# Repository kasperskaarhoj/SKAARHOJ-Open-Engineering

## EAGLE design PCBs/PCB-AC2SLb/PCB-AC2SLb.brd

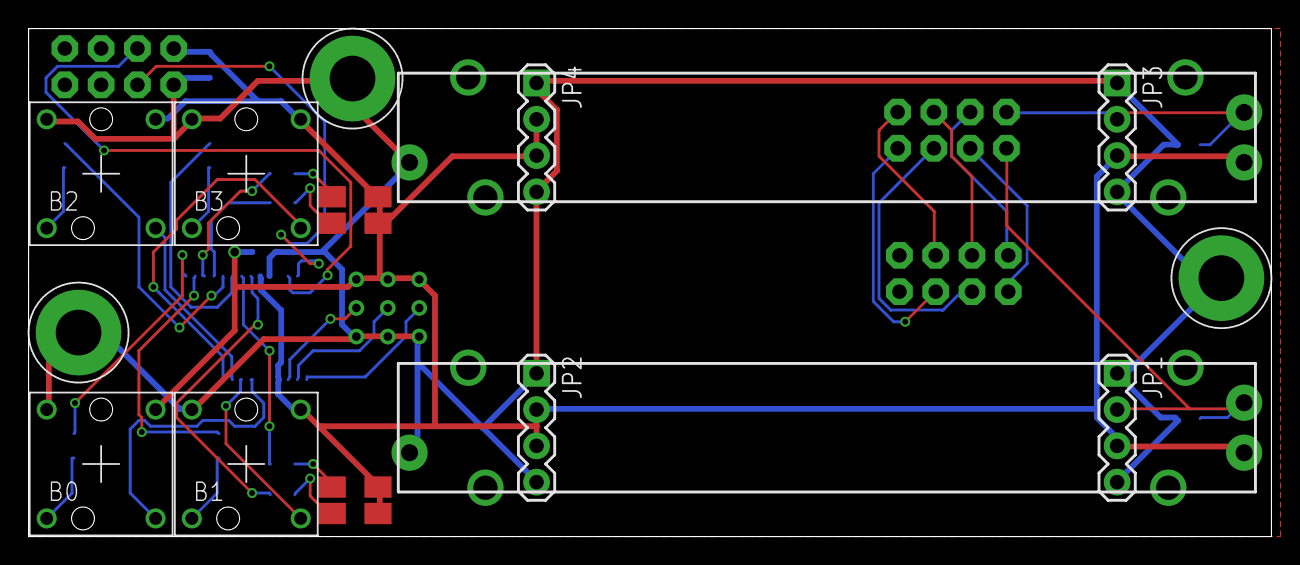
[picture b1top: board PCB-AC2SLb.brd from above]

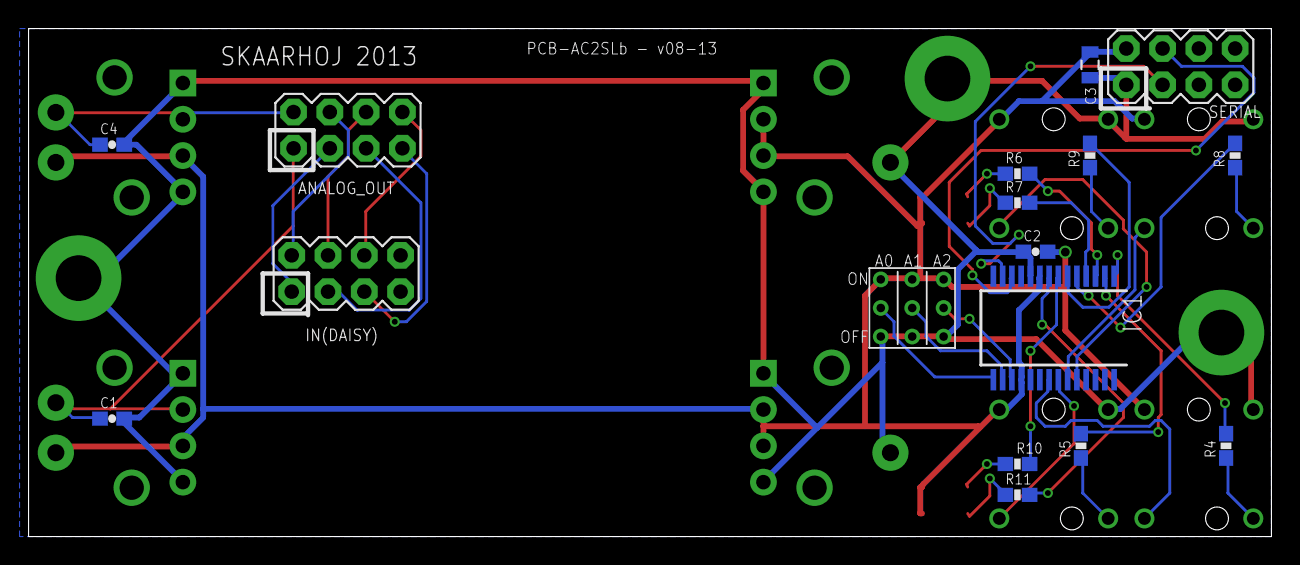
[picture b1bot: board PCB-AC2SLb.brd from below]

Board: 2 copper layers, 87.0 x 35.6 mm, 32 parts (17 on the bottom side), 35 nets.

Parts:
ANALOG_OUT: M04X2; 2X4
B0, B1, B2, B3: CFPB; CFPB-6/9MM
BILED1, BILED2: LEDBICOLOR-SMD
C1, C4: 10nF; 0603-CAP
C2: 100nF; 0603-CAP
C3: 10uF; 0805
IC1: MCP23017SS; SSOP28
IN(DAISY): M04X2; 2X4
JP1, JP2, JP3, JP4: 1X04
POT1, POT2: 10K; SLIDER45
R4, R5, R8, R9: 47R; 0603-RES
R6, R10: 820R; 0603-RES
R7, R11: 150R; 0603-RES
SERIAL: M04X2; 2X4
U$1, U$15, U$21: GNDPAD6MM; 3.2MMPAD6MM
U$19: 3BITADDR

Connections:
5V: B0.P$3, B1.P$3, B2.P$3, B3.P$3, BILED1.P$1, BILED1.P$3, BILED2.P$1, BILED2.P$3, C2.2, C3.1, IC1.9, IC1.18, JP1.3, JP2.2, JP2.3, JP3.3, JP4.2, JP4.3, POT1.1, POT2.1, SERIAL.2, U$19.H1, U$19.H2, U$19.H3
A0: IC1.15, U$19.A0
A1: IC1.16, U$19.A1
A2: IC1.17, U$19.A2
ANALOG1: ANALOG_OUT.1, C1.1, JP1.2, POT1.2A
ANALOG2: ANALOG_OUT.2, C4.1, JP3.2, POT2.2A
GND: B0.P$1, B1.P$1, B2.P$1, B3.P$1, C1.2, C2.1, C3.2, C4.2, IC1.10, JP1.1, JP1.4, JP2.1, JP2.4, JP3.1, JP3.4, JP4.1, JP4.4, POT1.3, POT2.3, SERIAL.1, U$1.P$1, U$15.P$1, U$19.L1, U$19.L2, U$19.L3, U$21.P$1
GPA0: B0.P$2, IC1.21
GPA1: B1.P$2, IC1.22
GPA2: B2.P$2, IC1.23
GPA3: B3.P$2, IC1.24
I2C_SCL: IC1.12, SERIAL.4
I2C_SDA: IC1.13, SERIAL.3
L0: B0.P$4, R4.1
L1: B1.P$4, R5.1
L2: BILED2.P$2, R6.1
L3: BILED2.P$4, R7.1
L4: B2.P$4, R8.1
L5: B3.P$4, R9.1
L6: BILED1.P$2, R10.1
L7: BILED1.P$4, R11.1
unnamed: IC1.4, R7.2
unnamed: IC1.5, R8.2
unnamed: IC1.6, R9.2
unnamed: IC1.7, R10.2
unnamed: IC1.8, R11.2
unnamed: IC1.3, R6.2
unnamed: IC1.2, R5.2
unnamed: IC1.1, R4.2
unnamed: ANALOG_OUT.3, IN(DAISY).1
unnamed: ANALOG_OUT.5, IN(DAISY).3
unnamed: ANALOG_OUT.7, IN(DAISY).5
unnamed: ANALOG_OUT.4, IN(DAISY).2
unnamed: ANALOG_OUT.6, IN(DAISY).4
unnamed: ANALOG_OUT.8, IN(DAISY).6

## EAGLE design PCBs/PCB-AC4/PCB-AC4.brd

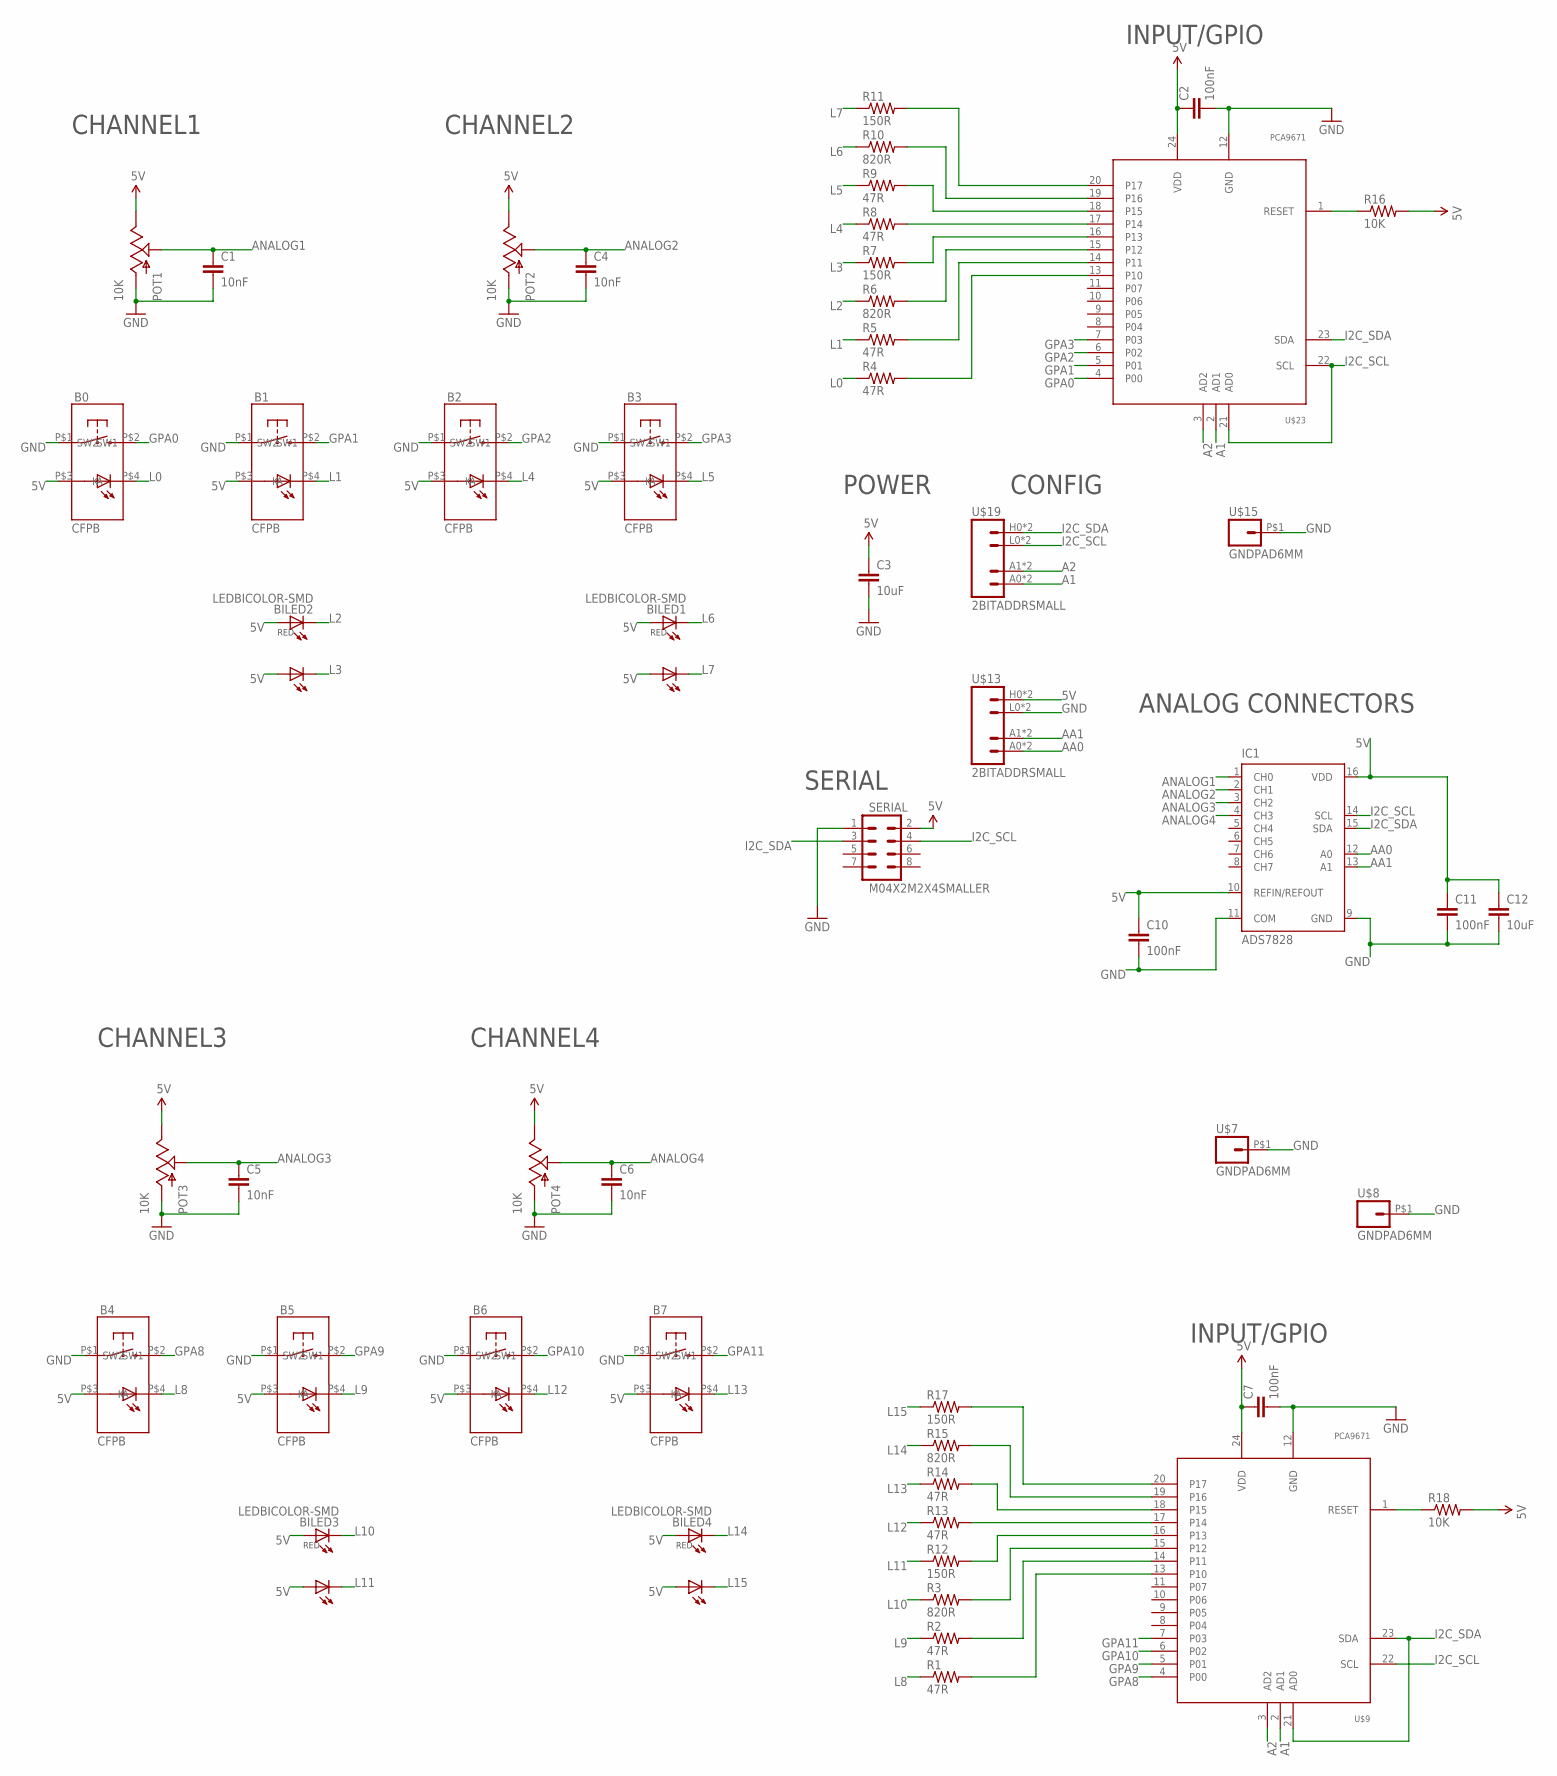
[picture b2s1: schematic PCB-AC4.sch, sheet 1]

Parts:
B0, B1, B2, B3, B4, B5, B6, B7: CFPB; CFPB-6/9MM
BILED1, BILED2, BILED3, BILED4: LEDBICOLOR-SMD
C1, C4, C5, C6: 10nF; 0603-CAP
C2, C7, C10, C11: 100nF; 0603-CAP
C3, C12: 10uF; 0805
IC1: ADS7828; TSSOP16-PW
POT1, POT2, POT3, POT4: 10K; ALPS_POT
R1, R2, R4, R5, R8, R9, R13, R14: 47R; 0603-RES
R3, R6, R10, R15: 820R; 0603-RES
R7, R11, R12, R17: 150R; 0603-RES
R16, R18: 10K; 0603-RES
SERIAL: M04X2M2X4SMALLER; M2X4SMALLER
U$7, U$8, U$15: GNDPAD6MM; 3.2MMPAD6MM
U$9, U$23: PCA9671; TSSOP24
U$13, U$19: 2BITADDRSMALL; 2BITADDR_SMALL

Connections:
5V: B0.P$3 (A), B1.P$3 (A), B2.P$3 (A), B3.P$3 (A), B4.P$3 (A), B5.P$3 (A), B6.P$3 (A), B7.P$3 (A), BILED1.P$1 (A), BILED1.P$3 (A1), BILED2.P$1 (A), BILED2.P$3 (A1), BILED3.P$1 (A), BILED3.P$3 (A1), BILED4.P$1 (A), BILED4.P$3 (A1), C2.1, C3.1, C7.1, C10.1, C11.1, C12.1, IC1.10 (REFIN/REFOUT), IC1.16 (VDD), POT1.P$1 (E), POT2.P$1 (E), POT3.P$1 (E), POT4.P$1 (E), R16.2, R18.2, SERIAL.2, U$9.24 (VDD), U$13.H0 (VCC), U$13.H1 (VCC), U$23.24 (VDD)
A1: U$9.2 (AD1), U$19.A0 (A1), U$19.AS0 (A1), U$23.2 (AD1)
A2: U$9.3 (AD2), U$19.A1 (A2), U$19.AS1 (A2), U$23.3 (AD2)
AA0: IC1.12 (A0), U$13.A0 (A1), U$13.AS0 (A1)
AA1: IC1.13 (A1), U$13.A1 (A2), U$13.AS1 (A2)
ANALOG1: C1.1, IC1.1 (CH0), POT1.P$2 (S)
ANALOG2: C4.1, IC1.2 (CH1), POT2.P$2 (S)
ANALOG3: C5.1, IC1.3 (CH2), POT3.P$2 (S)
ANALOG4: C6.1, IC1.4 (CH3), POT4.P$2 (S)
GND: B0.P$1 (SW1), B1.P$1 (SW1), B2.P$1 (SW1), B3.P$1 (SW1), B4.P$1 (SW1), B5.P$1 (SW1), B6.P$1 (SW1), B7.P$1 (SW1), C1.2, C2.2, C3.2, C4.2, C5.2, C6.2, C7.2, C10.2, C11.2, C12.2, IC1.9 (GND), IC1.11 (COM), POT1.P$3 (A), POT2.P$3 (A), POT3.P$3 (A), POT4.P$3 (A), SERIAL.1, U$7.P$1, U$8.P$1, U$9.12 (GND), U$13.L0 (GND), U$13.L1 (GND), U$15.P$1, U$23.12 (GND)
GPA0: B0.P$2 (SW2), U$23.4 (P00)
GPA1: B1.P$2 (SW2), U$23.5 (P01)
GPA2: B2.P$2 (SW2), U$23.6 (P02)
GPA3: B3.P$2 (SW2), U$23.7 (P03)
GPA8: B4.P$2 (SW2), U$9.4 (P00)
GPA9: B5.P$2 (SW2), U$9.5 (P01)
GPA10: B6.P$2 (SW2), U$9.6 (P02)
GPA11: B7.P$2 (SW2), U$9.7 (P03)
I2C_SCL: IC1.14 (SCL), SERIAL.4, U$9.22 (SCL), U$19.L0 (GND), U$19.L1 (GND), U$23.21 (AD0), U$23.22 (SCL)
I2C_SDA: IC1.15 (SDA), SERIAL.3, U$9.21 (AD0), U$9.23 (SDA), U$19.H0 (VCC), U$19.H1 (VCC), U$23.23 (SDA)
L0: B0.P$4 (K), R4.1
L1: B1.P$4 (K), R5.1
L2: BILED2.P$2 (C), R6.1
L3: BILED2.P$4 (C1), R7.1
L4: B2.P$4 (K), R8.1
L5: B3.P$4 (K), R9.1
L6: BILED1.P$2 (C), R10.1
L7: BILED1.P$4 (C1), R11.1
L8: B4.P$4 (K), R1.1
L9: B5.P$4 (K), R2.1
L10: BILED3.P$2 (C), R3.1
L11: BILED3.P$4 (C1), R12.1
L12: B6.P$4 (K), R13.1
L13: B7.P$4 (K), R14.1
L14: BILED4.P$2 (C), R15.1
L15: BILED4.P$4 (C1), R17.1
unnamed: R12.2, U$9.16 (P13)
unnamed: R7.2, U$23.16 (P13)
unnamed: R8.2, U$23.17 (P14)
unnamed: R9.2, U$23.18 (P15)
unnamed: R10.2, U$23.19 (P16)
unnamed: R11.2, U$23.20 (P17)
unnamed: R6.2, U$23.15 (P12)
unnamed: R5.2, U$23.14 (P11)
unnamed: R4.2, U$23.13 (P10)
unnamed: R13.2, U$9.17 (P14)
unnamed: R14.2, U$9.18 (P15)
unnamed: R15.2, U$9.19 (P16)
unnamed: R17.2, U$9.20 (P17)
unnamed: R3.2, U$9.15 (P12)
unnamed: R2.2, U$9.14 (P11)
unnamed: R1.2, U$9.13 (P10)
unnamed: R18.1, U$9.1 (RESET)
unnamed: R16.1, U$23.1 (RESET)

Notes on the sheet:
SERIAL
INPUT/GPIO
POWER
ANALOG CONNECTORS
CHANNEL1
CHANNEL2
CONFIG
CHANNEL3
CHANNEL4

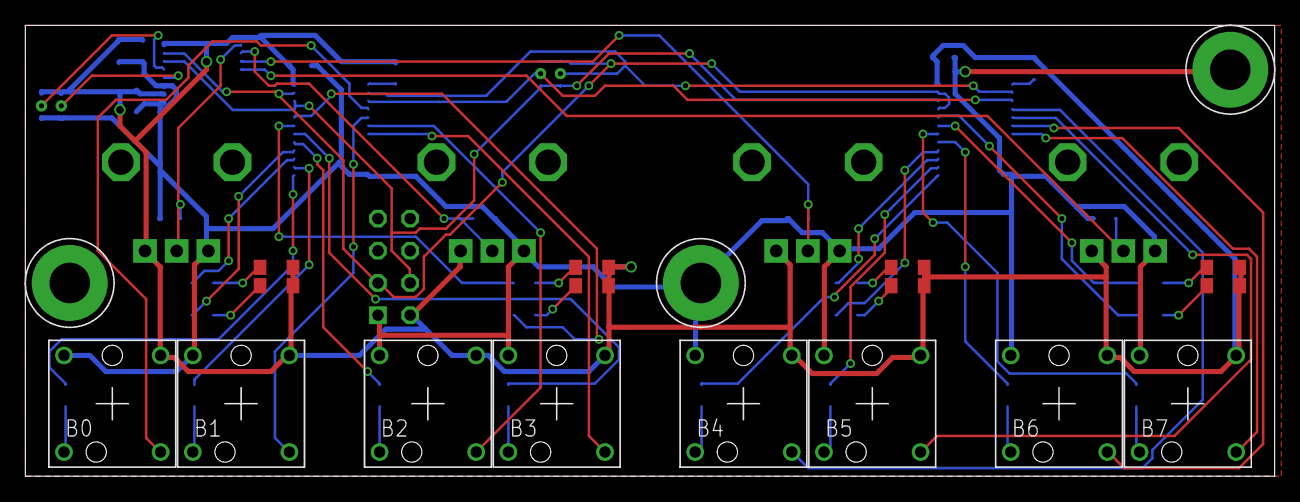
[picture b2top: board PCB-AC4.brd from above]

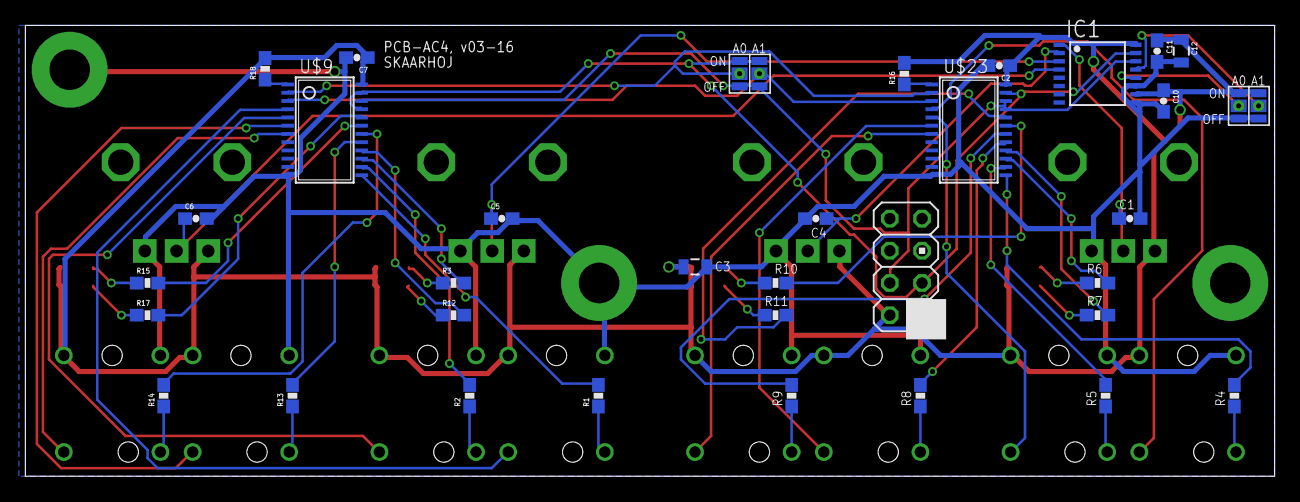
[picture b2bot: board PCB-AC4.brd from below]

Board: 2 copper layers, 98.5 x 35.6 mm, 53 parts (34 on the bottom side), 54 nets.

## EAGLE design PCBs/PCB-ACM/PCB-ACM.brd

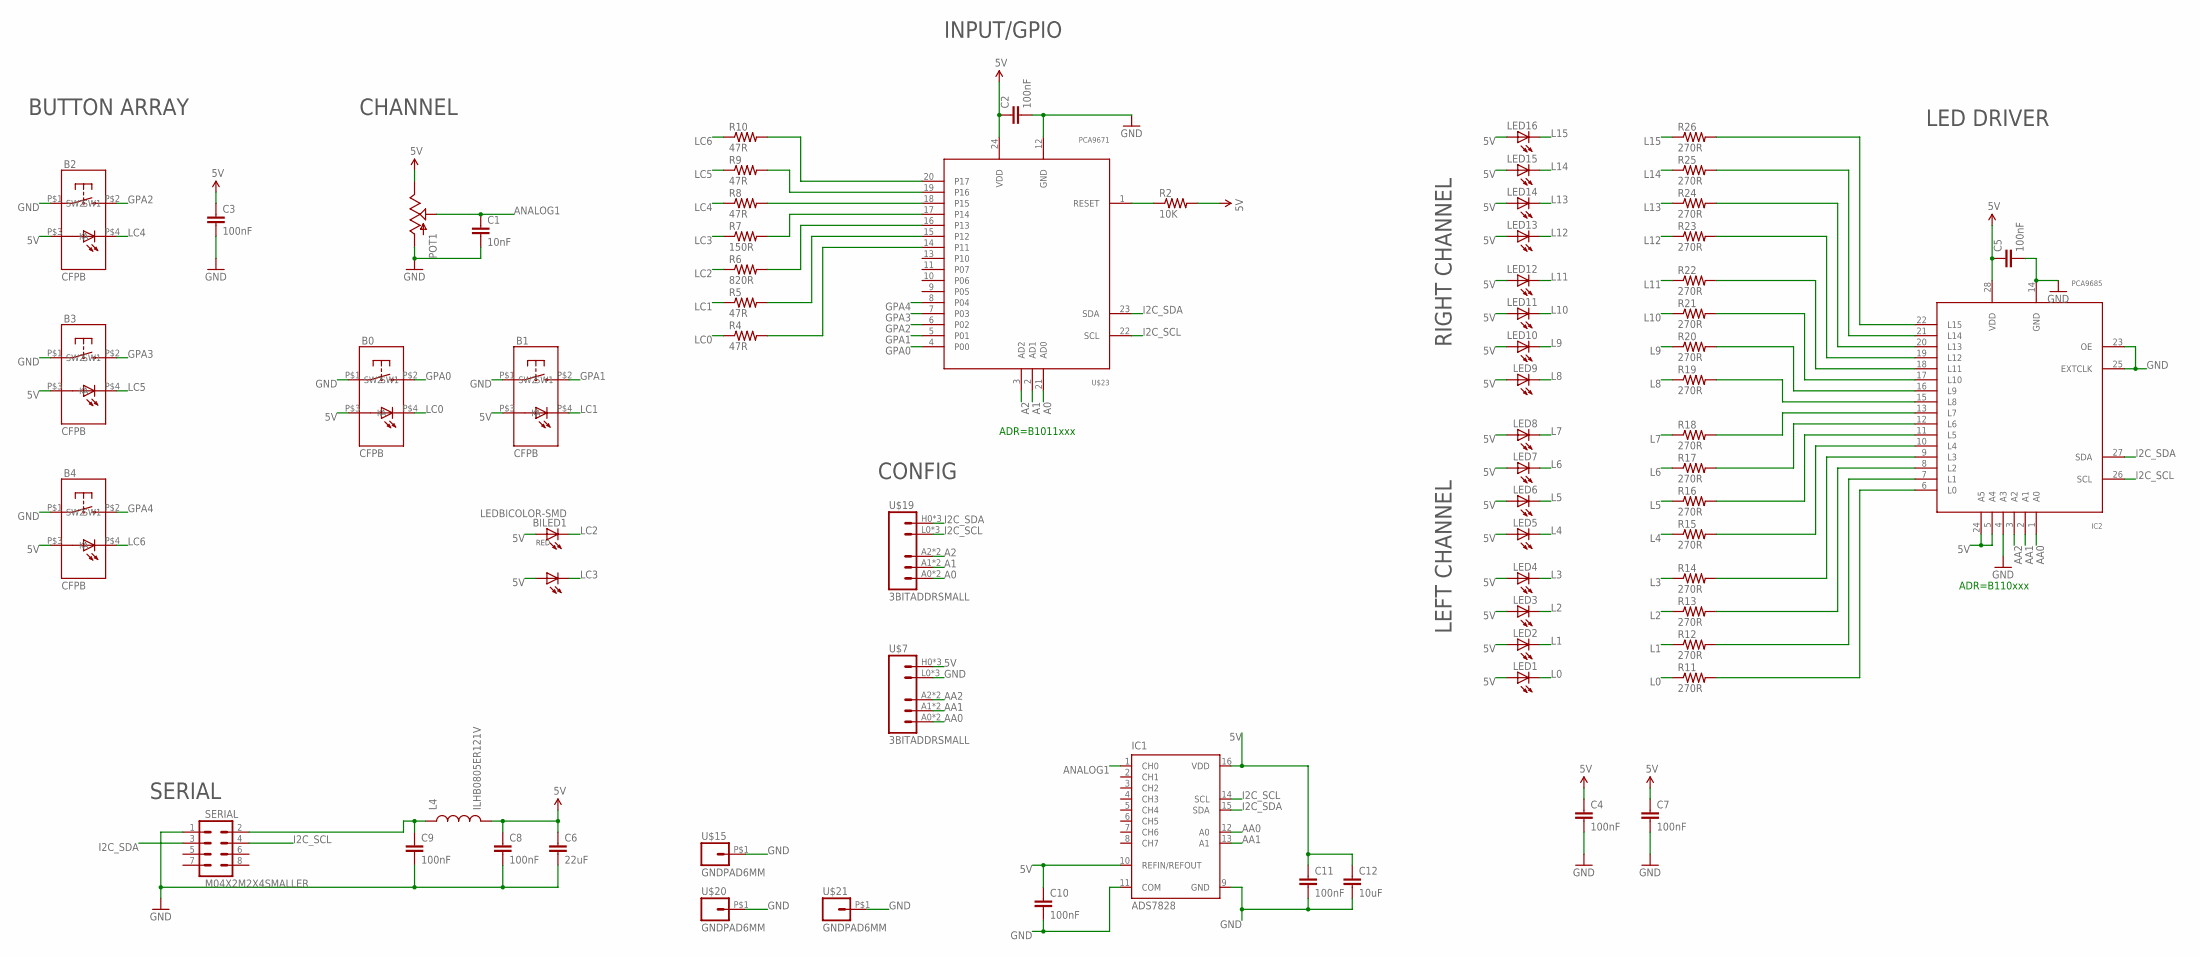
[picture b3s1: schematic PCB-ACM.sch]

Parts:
B0, B1, B2, B3, B4: CFPB; CFPB-6/9MM
BILED1: LEDBICOLOR-SMD
C1: 10nF; 0603-CAP
C2, C3, C4, C5, C7, C8, C9, C10, C11: 100nF; 0603-CAP
C6: 22uF; 0805
C12: 10uF; 0805
IC1: ADS7828; TSSOP16-PW
IC2: PCA9685; TSSOP28
L4: ILHB0805ER121V; 0805
LED1, LED2, LED3, LED4, LED5, LED6, LED7, LED8, LED9, LED10, LED11, LED12, LED13, LED14, LED15, LED16: LED3MM
POT1: POT; ALPS_POT
R2: 10K; 0603-RES
R4, R5, R8, R9, R10: 47R; 0603-RES
R6: 820R; 0603-RES
R7: 150R; 0603-RES
R11, R12, R13, R14, R15, R16, R17, R18, R19, R20, R21, R22, R23, R24, R25, R26: 270R; 0603-RES
SERIAL: M04X2M2X4SMALLER; M2X4SMALLER
U$7, U$19: 3BITADDRSMALL; 3BITADDR_SMALL
U$15, U$20, U$21: GNDPAD6MM; 3.2MMPAD6MM
U$23: PCA9671; TSSOP24

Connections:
5V: B0.P$3 (A), B1.P$3 (A), B2.P$3 (A), B3.P$3 (A), B4.P$3 (A), BILED1.P$1 (A), BILED1.P$3 (A1), C2.1, C3.1, C4.1, C5.1, C6.1, C7.1, C8.1, C10.1, C11.1, C12.1, IC1.10 (REFIN/REFOUT), IC1.16 (VDD), IC2.5 (A4), IC2.24 (A5), IC2.28 (VDD), L4.2, LED1.A, LED2.A, LED3.A, LED4.A, LED5.A, LED6.A, LED7.A, LED8.A, LED9.A, LED10.A, LED11.A, LED12.A, LED13.A, LED14.A, LED15.A, LED16.A, POT1.P$1 (E), R2.2, U$7.H0 (VCC), U$7.H1 (VCC), U$7.H2 (VCC), U$23.24 (VDD)
A0: U$19.A0, U$19.AS0 (A0), U$23.21 (AD0)
A1: U$19.A1, U$19.AS1 (A1), U$23.2 (AD1)
A2: U$19.A2, U$19.AS2 (A2), U$23.3 (AD2)
AA0: IC1.12 (A0), IC2.1 (A0), U$7.A0, U$7.AS0 (A0)
AA1: IC1.13 (A1), IC2.2 (A1), U$7.A1, U$7.AS1 (A1)
AA2: IC2.3 (A2), U$7.A2, U$7.AS2 (A2)
ANALOG1: C1.1, IC1.1 (CH0), POT1.P$2 (S)
ARD_5V: C9.1, L4.1, SERIAL.2
GND: B0.P$1 (SW1), B1.P$1 (SW1), B2.P$1 (SW1), B3.P$1 (SW1), B4.P$1 (SW1), C1.2, C2.2, C3.2, C4.2, C5.2, C6.2, C7.2, C8.2, C9.2, C10.2, C11.2, C12.2, IC1.9 (GND), IC1.11 (COM), IC2.4 (A3), IC2.14 (GND), IC2.23 (OE), IC2.25 (EXTCLK), POT1.P$3 (A), SERIAL.1, U$7.L0 (GND), U$7.L1 (GND), U$7.L2 (GND), U$15.P$1, U$20.P$1, U$21.P$1, U$23.12 (GND)
GPA0: B0.P$2 (SW2), U$23.4 (P00)
GPA1: B1.P$2 (SW2), U$23.5 (P01)
GPA2: B2.P$2 (SW2), U$23.6 (P02)
GPA3: B3.P$2 (SW2), U$23.7 (P03)
GPA4: B4.P$2 (SW2), U$23.8 (P04)
I2C_SCL: IC1.14 (SCL), IC2.26 (SCL), SERIAL.4, U$19.L0 (GND), U$19.L1 (GND), U$19.L2 (GND), U$23.22 (SCL)
I2C_SDA: IC1.15 (SDA), IC2.27 (SDA), SERIAL.3, U$19.H0 (VCC), U$19.H1 (VCC), U$19.H2 (VCC), U$23.23 (SDA)
L0: LED1.K (C), R11.1
L1: LED2.K (C), R12.1
L2: LED3.K (C), R13.1
L3: LED4.K (C), R14.1
L4: LED5.K (C), R15.1
L5: LED6.K (C), R16.1
L6: LED7.K (C), R17.1
L7: LED8.K (C), R18.1
L8: LED9.K (C), R19.1
L9: LED10.K (C), R20.1
L10: LED11.K (C), R21.1
L11: LED12.K (C), R22.1
L12: LED13.K (C), R23.1
L13: LED14.K (C), R24.1
L14: LED15.K (C), R25.1
L15: LED16.K (C), R26.1
LC0: B0.P$4 (K), R4.1
LC1: B1.P$4 (K), R5.1
LC2: BILED1.P$2 (C), R6.1
LC3: BILED1.P$4 (C1), R7.1
LC4: B2.P$4 (K), R8.1
LC5: B3.P$4 (K), R9.1
LC6: B4.P$4 (K), R10.1
unnamed: IC2.13 (L7), R18.2
unnamed: R7.2, U$23.17 (P14)
unnamed: R8.2, U$23.18 (P15)
unnamed: R9.2, U$23.19 (P16)
unnamed: R10.2, U$23.20 (P17)
unnamed: R2.1, U$23.1 (RESET)
unnamed: R6.2, U$23.16 (P13)
unnamed: R5.2, U$23.15 (P12)
unnamed: R4.2, U$23.14 (P11)
unnamed: IC2.12 (L6), R17.2
unnamed: IC2.11 (L5), R16.2
unnamed: IC2.10 (L4), R15.2
unnamed: IC2.9 (L3), R14.2
unnamed: IC2.8 (L2), R13.2
unnamed: IC2.7 (L1), R12.2
unnamed: IC2.6 (L0), R11.2
unnamed: IC2.15 (L8), R19.2
unnamed: IC2.16 (L9), R20.2
unnamed: IC2.17 (L10), R21.2
unnamed: IC2.18 (L11), R22.2
unnamed: IC2.19 (L12), R23.2
unnamed: IC2.20 (L13), R24.2
unnamed: IC2.21 (L14), R25.2
unnamed: IC2.22 (L15), R26.2

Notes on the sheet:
SERIAL
INPUT/GPIO
CHANNEL
ADR=B110xxx
LED DRIVER
LEFT CHANNEL
RIGHT CHANNEL
BUTTON ARRAY
ADR=B1011xxx
CONFIG

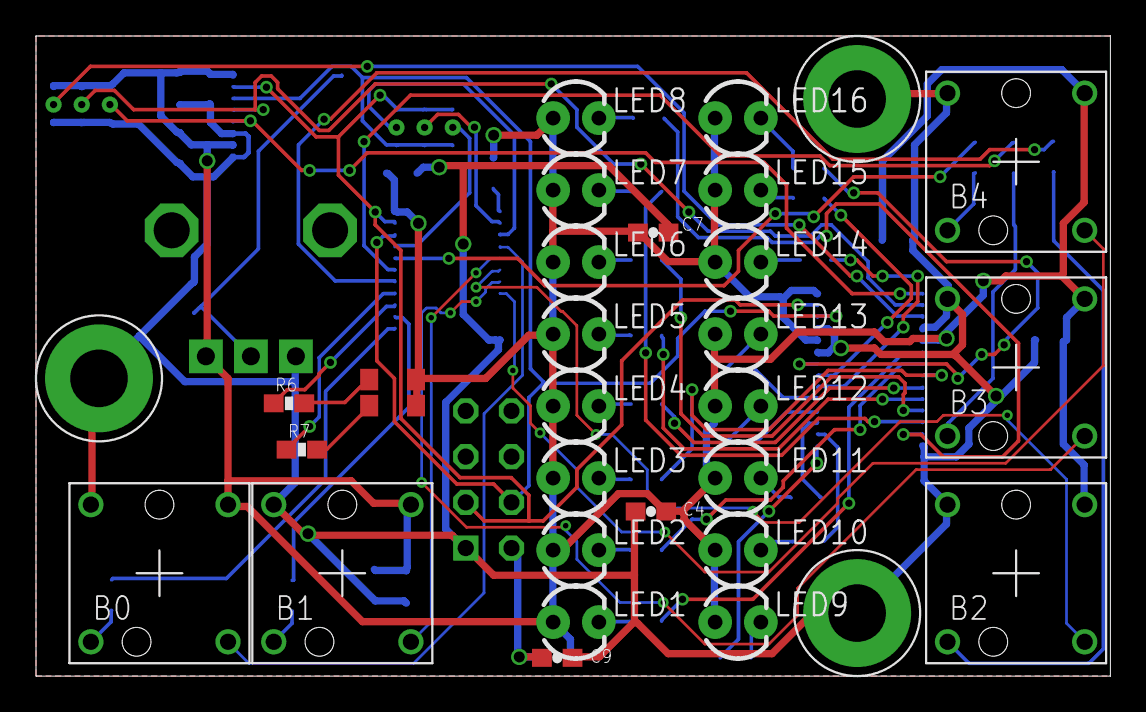
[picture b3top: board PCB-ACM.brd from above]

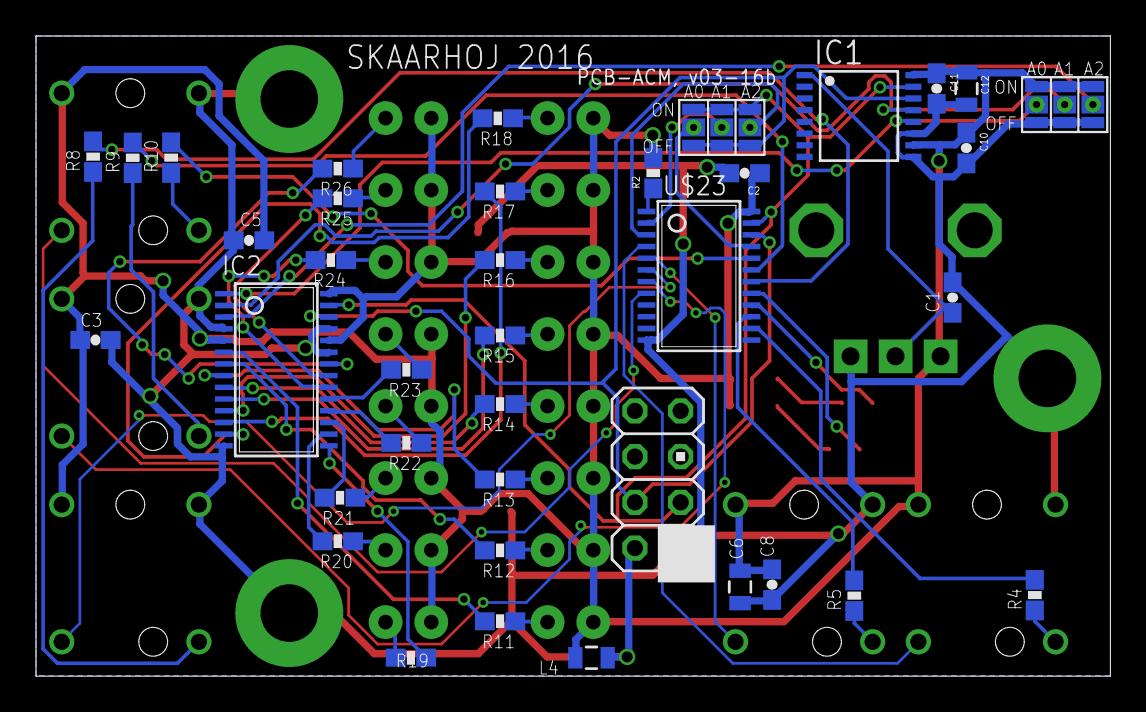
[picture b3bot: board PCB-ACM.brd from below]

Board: 2 copper layers, 59.7 x 35.6 mm, 69 parts (38 on the bottom side), 64 nets.

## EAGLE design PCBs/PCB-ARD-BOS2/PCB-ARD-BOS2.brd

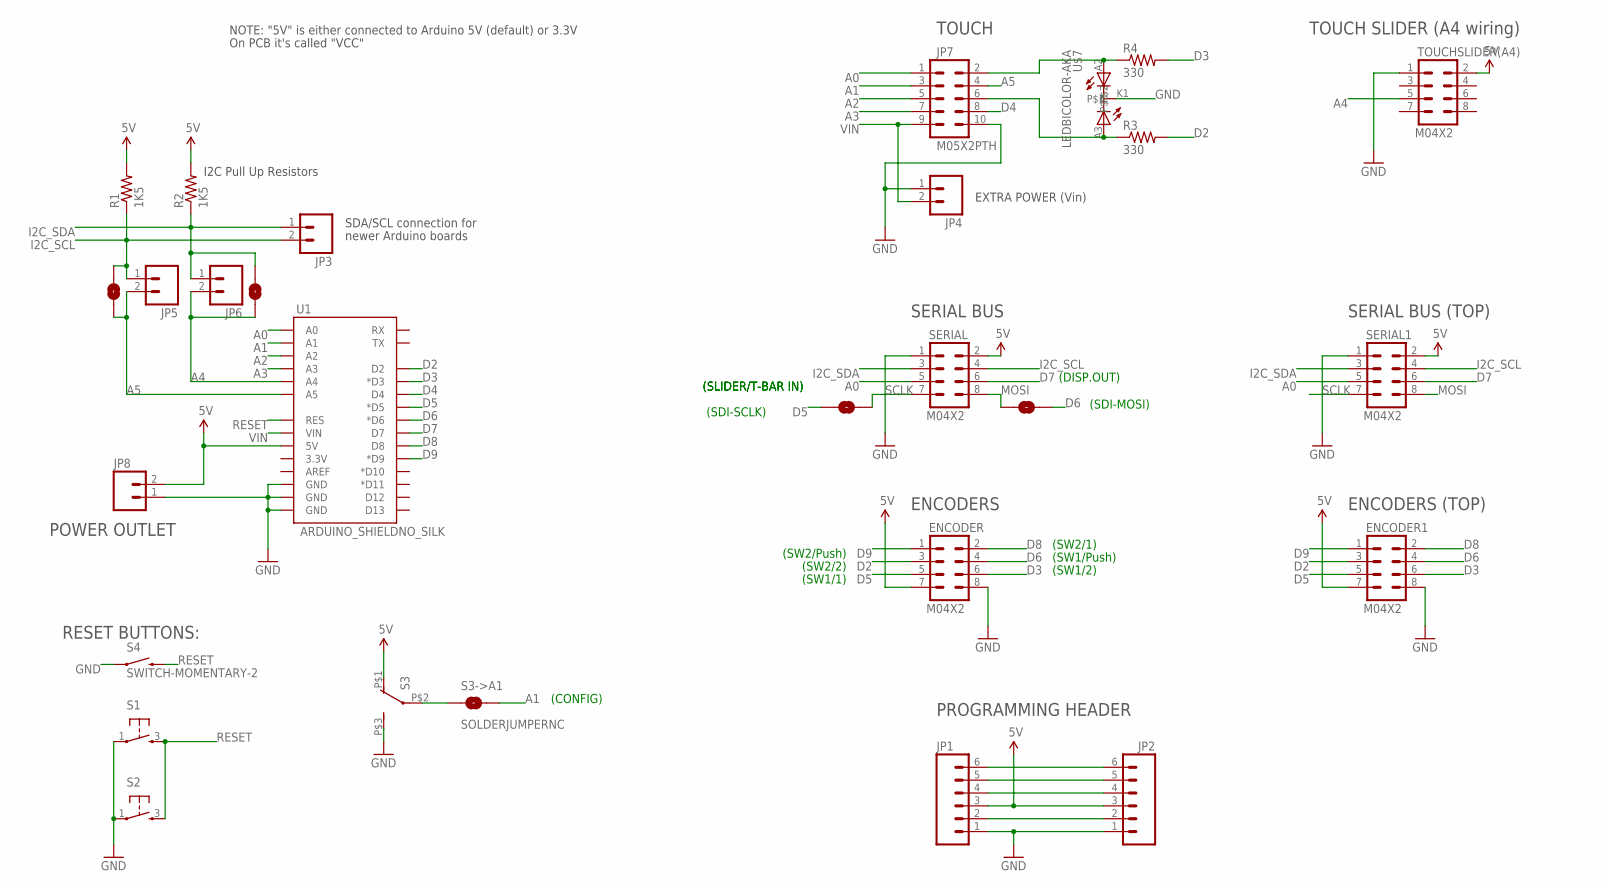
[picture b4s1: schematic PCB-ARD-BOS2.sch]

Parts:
ENCODER, ENCODER1: M04X2; 2X4
JP1, JP2: M06POLAR; MOLEX-1X6
JP3, JP4, JP5, JP6: M02PTH; 1X02
JP7: M05X2PTH; AVR_ICSP
JP8: M02PTH4; 1X02_XTRA_BIG
MOSI->D6: SOLDERJUMPERNC; SJ_2S
R1, R2: 1K5; 0603-RES
R3, R4: 330; AXIAL-0.4
S1, S2: TAC_SWITCH; PUSHBUTTON
S3: SWITCH-DPST; TECONNECTIVITY-DPST
S3->A1, S3->A2, S3->A3: SOLDERJUMPERNC; SJ_2S
S4: SWITCH-MOMENTARY-2; TACTILE_SWITCH_TALL
SCLK->D5: SOLDERJUMPERNC; SJ_2S
SERIAL, SERIAL1: M04X2; 2X4
TOUCHSLIDER(A4): M04X2; 2X4
U1: ARDUINO_SHIELDNO_SILK; DUEMILANOVE_VIAS
U$7: LEDBICOLOR-AKA; LED5MM-BICOLOR

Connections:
5V: ENCODER.7, ENCODER1.7, JP1.3, JP2.3, JP8.2, R1.2, R2.2, S3.P$1 (O), SERIAL.2, SERIAL1.2, TOUCHSLIDER(A4).2, U1.5V
A0: JP7.1, SERIAL.5, SERIAL1.5, U1.A0
A1: JP7.3, S3->A1.2, U1.A1
A2: JP7.5, U1.A2
A3: JP7.7, U1.A3
A4: JP6.2, S3->A3.2, TOUCHSLIDER(A4).5, U1.A4
A5: JP5.2, JP7.4, S3->A2.2, U1.A5
D2: ENCODER.3, ENCODER1.3, R3.P$2 (2), U1.D2
D3: ENCODER.6, ENCODER1.6, R4.P$2 (2), U1.D3 (*D3)
D4: JP7.8, U1.D4
D5: ENCODER.5, ENCODER1.5, SCLK->D5.1, U1.D5 (*D5)
D6: ENCODER.4, ENCODER1.4, MOSI->D6.2, U1.D6 (*D6)
D7: SERIAL.6, SERIAL1.6, U1.D7
D8: ENCODER.2, ENCODER1.2, U1.D8
D9: ENCODER.1, ENCODER1.1, U1.D9 (*D9)
GND: ENCODER.8, ENCODER1.8, JP1.1, JP2.1, JP4.1, JP7.10, JP8.1, S1.1, S2.1, S3.P$3 (S), S4.A2 (1), SERIAL.1, SERIAL1.1, TOUCHSLIDER(A4).1, U1.GND@0 (GND), U1.GND@1 (GND), U1.GND@2 (GND), U$7.K1
I2C_SCL: JP3.2, JP5.1, R1.1, S3->A2.1, SERIAL.4, SERIAL1.4
I2C_SDA: JP3.1, JP6.1, R2.1, S3->A3.1, SERIAL.3, SERIAL1.3
MOSI: MOSI->D6.1, SERIAL.8, SERIAL1.8
unnamed: JP1.2, JP2.2
unnamed: S3.P$2, S3->A1.1
unnamed: JP7.2, R4.P$1 (1), U$7.A2
unnamed: JP7.6, R3.P$1 (1), U$7.A3
unnamed: JP1.4, JP2.4
unnamed: JP1.5, JP2.5
unnamed: JP1.6, JP2.6
RESET: S1.3, S2.3, S4.B2 (2), U1.RES
SCLK: SCLK->D5.2, SERIAL.7, SERIAL1.7
VIN: JP4.2, JP7.9, U1.VIN

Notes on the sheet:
PROGRAMMING HEADER
I2C Pull Up Resistors
SDA/SCL connection for
newer Arduino boards
ENCODERS
SERIAL BUS
TOUCH
POWER OUTLET
EXTRA POWER (Vin)
(SLIDER/T-BAR IN)
(SDI-SCLK)
(SDI-MOSI)
(SW2/Push)
(SW2/2)
(SW1/1)
(SW2/1)
(SW1/Push)
(SW1/2)
(CONFIG)
ENCODERS (TOP)
SERIAL BUS (TOP)
(DISP.OUT)
TOUCH SLIDER (A4 wiring)
RESET BUTTONS:
NOTE: "5V" is either connected to Arduino 5V (default) or 3.3V
On PCB it's called "VCC"

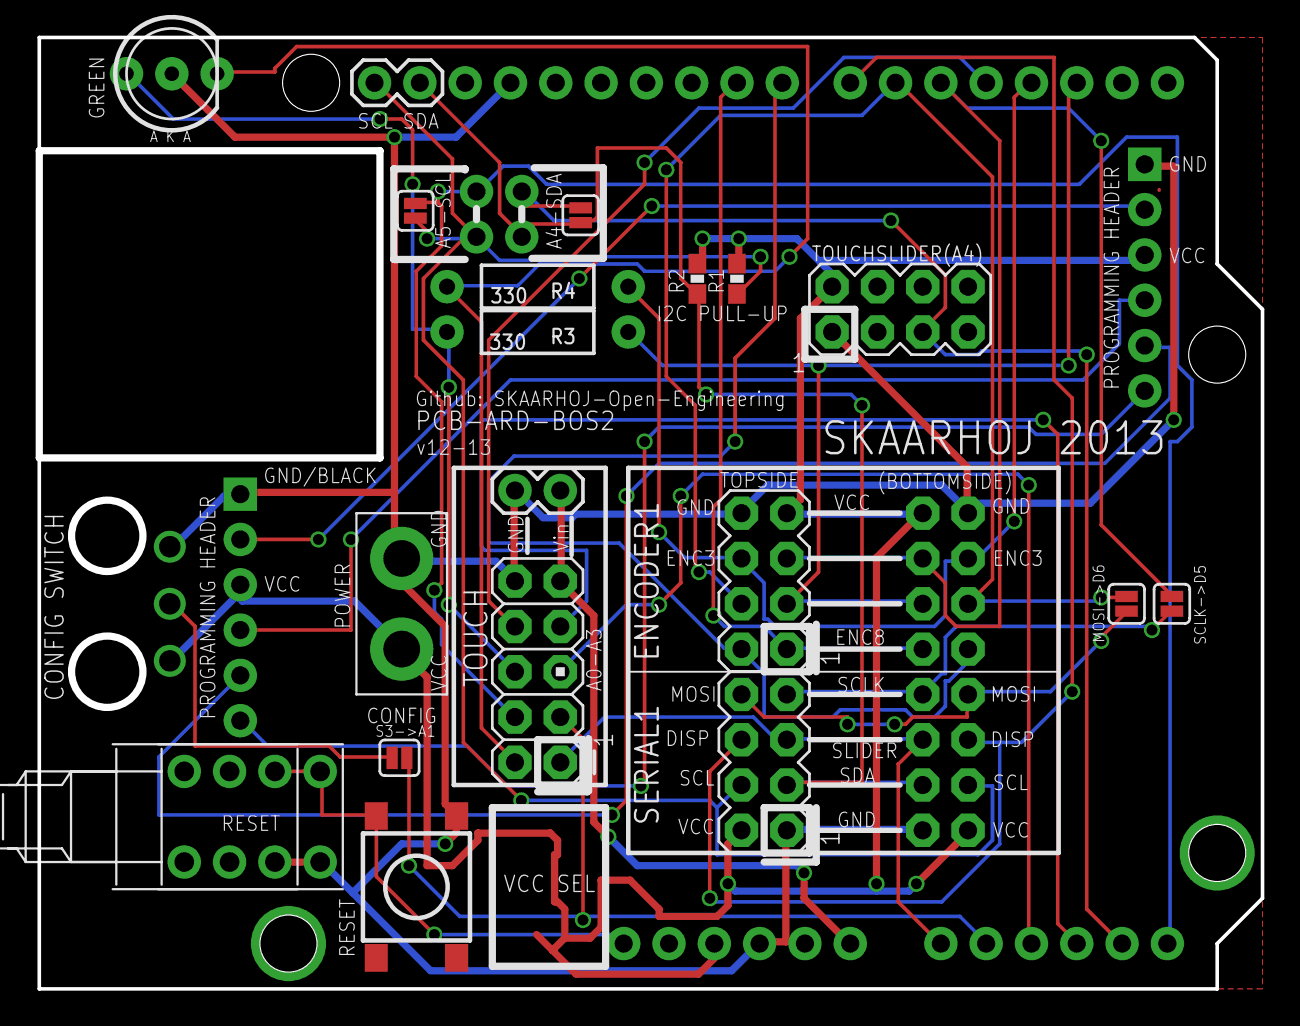
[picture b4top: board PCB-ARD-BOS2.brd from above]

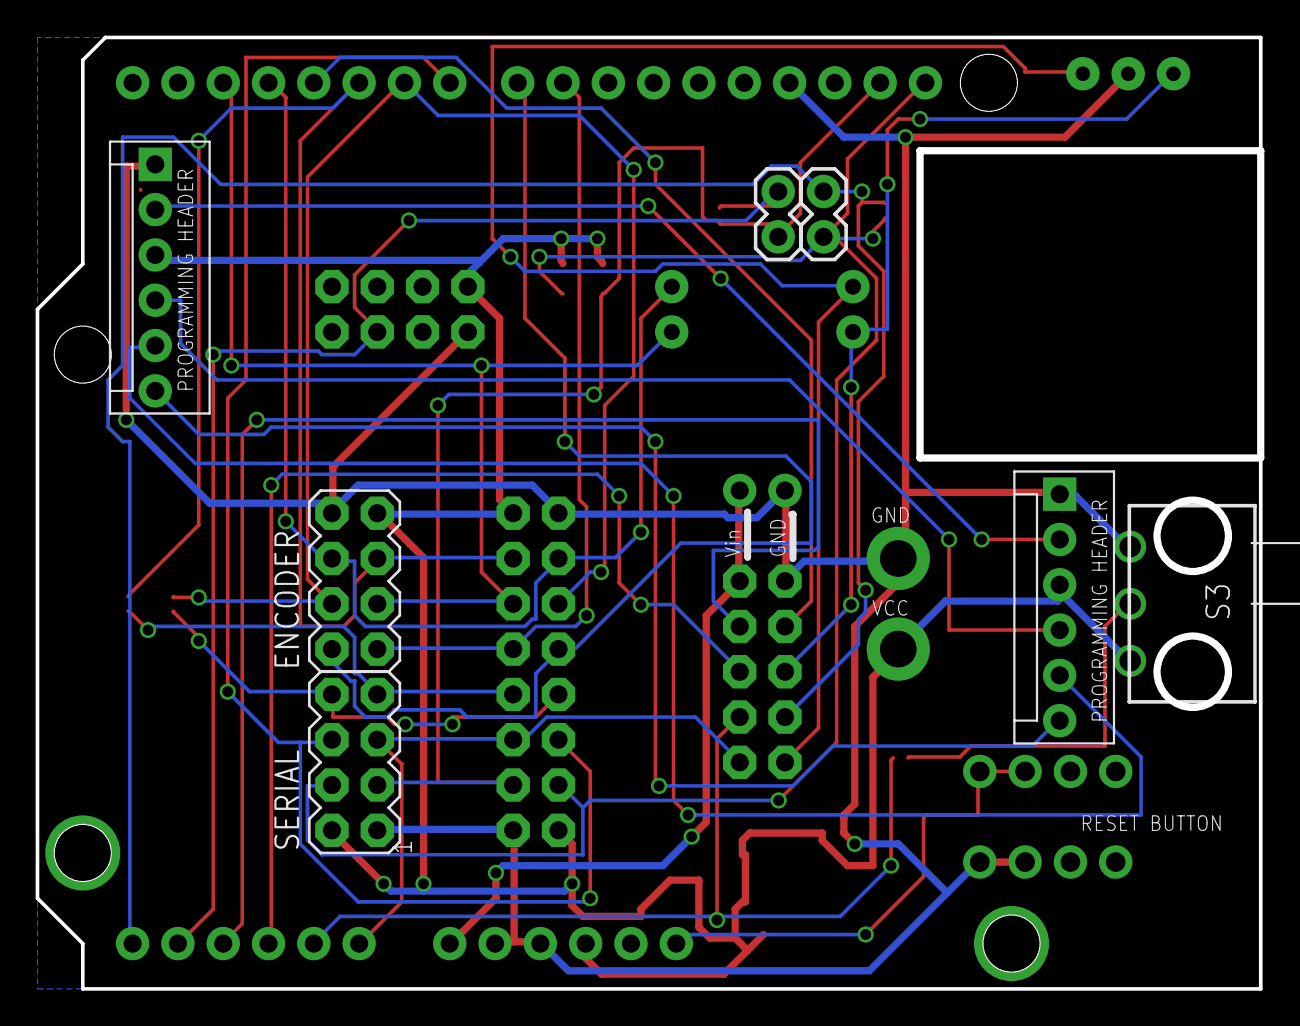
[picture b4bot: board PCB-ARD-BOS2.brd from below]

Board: 2 copper layers, 68.6 x 53.3 mm, 29 parts (7 on the bottom side), 29 nets.

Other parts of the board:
U$8: ARDUINO-OUTLINE

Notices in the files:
parts and their libraries:
SparkFun: Licensing: CC v3.0 Share-Alike You are welcome to use this library for commercial purposes.
